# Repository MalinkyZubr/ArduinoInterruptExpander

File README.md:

Driver library for custom virtual interrupt board designed for arduino uno

Personal project of mine when I realized there are only 2 external interrupts on an arduino uno. Designed a digital logic board to serialize input from 32 external devices (buttons etc) into a single interrupt pin, hence there are 32 'virtual' interrupts

ideally, these act as normal interrupts, just requiring an additional layer of software abstraction to function.

In all likelihood you are probably better off upgrading to an arduino mega with more built in interrupt pins, since without an economy of scale im going to be using relatively large SMD logic chips on the board. Doesnt lend itself to small size. Still, feel free to use this, and assemble a board (when all this is done)

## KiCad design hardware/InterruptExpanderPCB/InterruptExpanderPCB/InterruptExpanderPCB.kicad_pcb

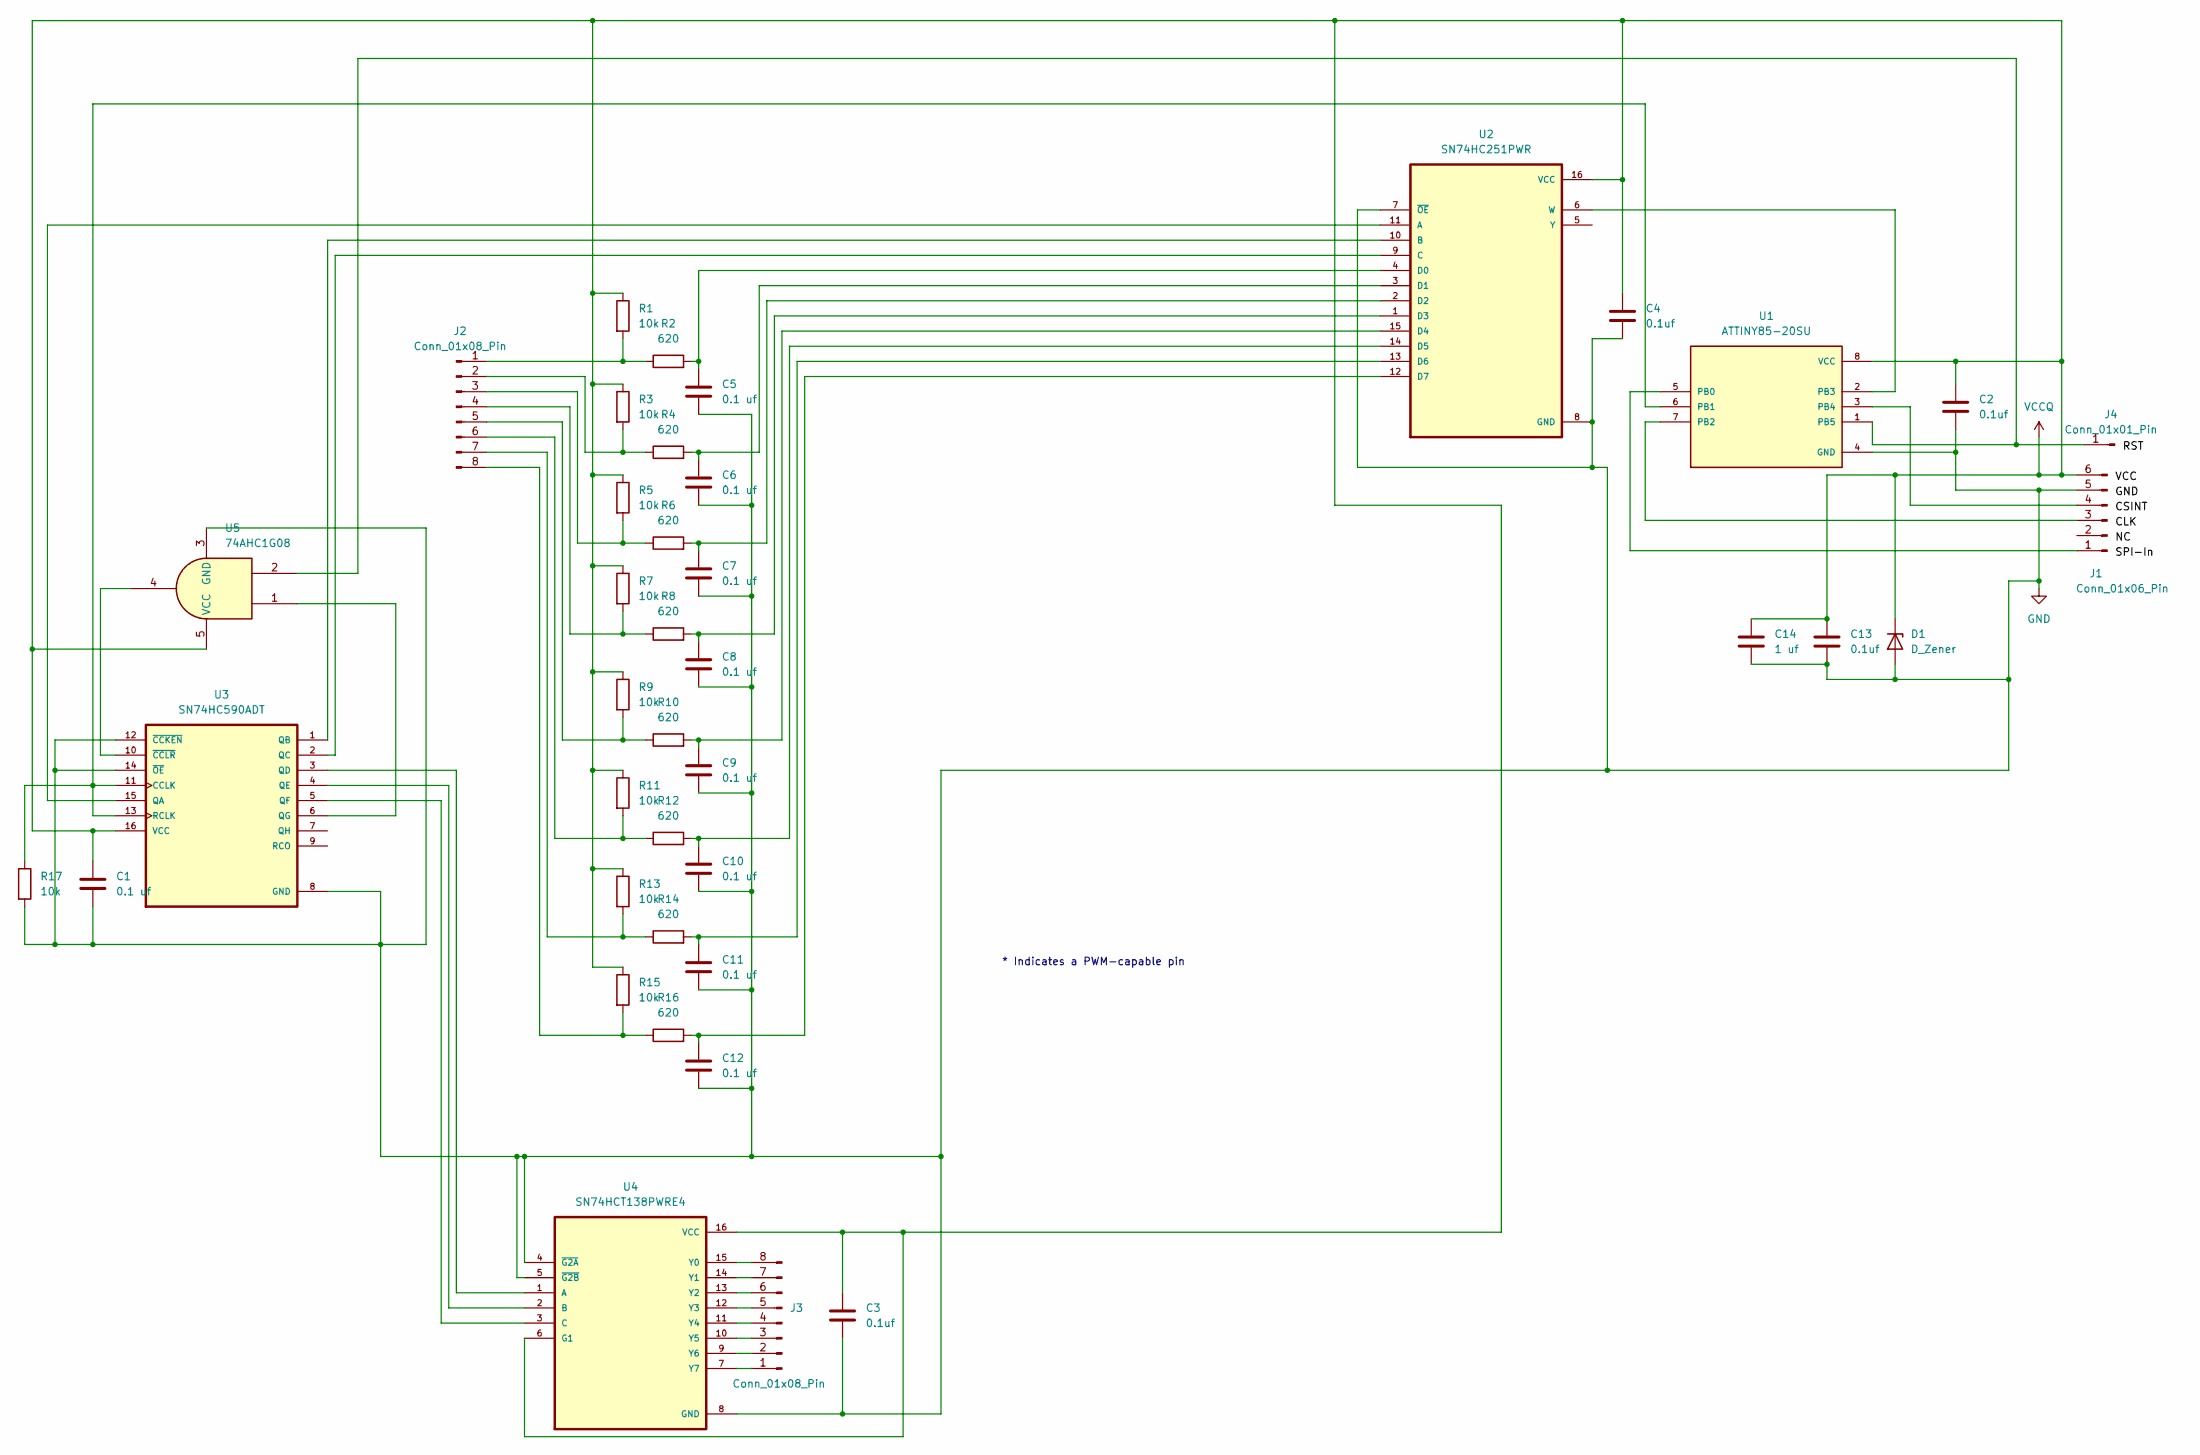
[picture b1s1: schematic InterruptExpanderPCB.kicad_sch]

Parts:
C1, C5, C6, C7, C8, C9, C10, C11, C12: 0.1 uf; C_0402_1005Metric
C2, C3, C4, C13: 0.1uf; C_0402_1005Metric
C14: 1 uf; C_0603_1608Metric
D1: D_Zener; D_SOD-123
J1: Conn_01x06_Pin; PinHeader_1x06_P2.00mm_Vertical
J2, J3: Conn_01x08_Pin; PinHeader_1x08_P2.00mm_Vertical
J4: Conn_01x01_Pin
R1, R3, R5, R7, R9, R11, R13, R15, R17: 10k; C_0402_1005Metric
R2, R4, R6, R8, R10, R12, R14, R16: 620; C_0402_1005Metric
U1: ATTINY85-20SU; SOIC127P798X216-8N; PARTREV 2586Q–AVR–08/2013
U2: SN74HC251PWR; SOP65P640X120-16N
U3: SN74HC590ADT; SOIC127P600X175-16N
U4: SN74HCT138PWRE4; SOP65P640X120-16N
U5: 74AHC1G08; SOT-353_SC-70-5_Handsoldering

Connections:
GND: C1.2, C2.2, C3.2, C4.2, C5.2, C6.2, C7.2, C8.2, C9.2, C10.2, C11.2, C12.2, C13.2, C14.2, D1.2 (A), J1.5, R17.2, U1.4 (GND), U2.7 (~OE), U2.8 (GND), U3.8 (GND), U3.12 (~CCKEN), U3.14 (~OE), U4.4 (~G2A), U4.5 (~G2B), U4.8 (GND), U5.3 (GND)
unnamed: J1.1, U1.5 (PB0)
unnamed: J1.3, U1.7 (PB2)
unnamed: J1.4, U1.3 (PB4)
unnamed: J2.1, R1.2, R2.1
unnamed: J2.2, R3.2, R4.1
unnamed: J2.3, R5.2, R6.1
unnamed: J2.4, R7.2, R8.1
unnamed: J2.5, R9.2, R10.1
unnamed: J2.6, R11.2, R12.1
unnamed: J2.7, R13.2, R14.1
unnamed: J2.8, R15.2, R16.1
unnamed: J3.1, U4.7 (Y7)
unnamed: J3.2, U4.9 (Y6)
unnamed: J3.3, U4.10 (Y5)
unnamed: J3.4, U4.11 (Y4)
unnamed: J3.5, U4.12 (Y3)
unnamed: J3.6, U4.13 (Y2)
unnamed: J3.7, U4.14 (Y1)
unnamed: J3.8, U4.15 (Y0)
unnamed: J4.1, U1.1 (PB5), U5.2
unnamed: R17.1, U1.6 (PB1), U3.11 (CCLK), U3.13 (RCLK)
unnamed: U1.2 (PB3), U2.6 (W)
unnamed: U2.11 (A), U3.15 (QA)
unnamed: U2.10 (B), U3.1 (QB)
unnamed: U2.9 (C), U3.2 (QC)
unnamed: C5.1, R2.2, U2.4 (D0)
unnamed: C6.1, R4.2, U2.3 (D1)
unnamed: C7.1, R6.2, U2.2 (D2)
unnamed: C8.1, R8.2, U2.1 (D3)
unnamed: C9.1, R10.2, U2.15 (D4)
unnamed: C10.1, R12.2, U2.14 (D5)
unnamed: C11.1, R14.2, U2.13 (D6)
unnamed: C12.1, R16.2, U2.12 (D7)
unnamed: U3.3 (QD), U4.1 (A)
unnamed: U3.4 (QE), U4.2 (B)
unnamed: U3.5 (QF), U4.3 (C)
unnamed: U3.6 (QG), U5.1
unnamed: U3.10 (~CCLR), U5.4
VCCQ: C1.1, C2.1, C3.1, C4.1, C13.1, C14.1, D1.1 (K), J1.6, R1.1, R3.1, R5.1, R7.1, R9.1, R11.1, R13.1, R15.1, U1.8 (VCC), U2.16 (VCC), U3.16 (VCC), U4.6 (G1), U4.16 (VCC), U5.5 (VCC)

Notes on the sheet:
* Indicates a PWM-capable pin

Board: 4 copper layers, 40 parts (0 on the bottom side), 40 nets, no tracks yet.

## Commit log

2024-07-19 initial
2024-07-20 implementing timer interrupt setup, low level serial receive protocols on software side. Will upload schematics later
2024-07-24 designing quine mcluskey app for boolean simplification
2024-07-25 finished implementing quine mckluskey algorithm
2024-07-25 finished quine mcluskey
2024-07-25 working on lib
2024-07-25 added multisim schematics
2024-07-26 working on things
2024-08-02 restructuring. Started firmware in assembly
2024-08-03 finished first iteration of atiny85 assembly
2024-08-03 small edit
2024-08-03 reorganized some python code
2024-08-06 resolve
2024-08-06 working
2024-08-06 work
2024-08-07 working on makefile
2024-08-09 working on debugging, compilation for arduino
2024-08-09 working on compilation
2024-08-11 added new schematics
2024-08-14 stuff
2024-08-18 working on the makefile stuff
2024-09-02 working on tests
2024-09-02 Fully implemented tests, pushing finished product (until its time to upload to board for integration)
2024-09-02 finished finally compiling assembly
2024-09-02 Added auutomation for assembly tests in makefile, built out lab settings tests for the atiny firmware
2024-09-02 Fixed an issue identified with hardware for shared clock read and write functions. Fixed issue with SPI loop on firmware
2024-09-03 fixed minor issue with interrupt handling in VirtualInterruptBoard.h
2024-09-03 Added test subroutine that will traansmit actual interrupt address
2024-09-03 Created simple interrupt expander example
2024-09-03 added serial writes to the test
2024-09-05 Added builder + tests for builder
2024-09-07 Ran test codes with oscilloscope. COnfirmed function. Modified some sasemly
